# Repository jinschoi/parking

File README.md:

Ultrasonic Parking Aid
=======

Parking aid using the SR-04 ultrasonic distance sensor to indicate distance via LEDs. Low-power, AA battery powered, 3D printable enclosure suggestion available.

Green LED indicates go until yellow LED gets triggered at a set distance. Yellow LED blinks with a rate proportional to distance until red LED distance is crossed. LED blinking rate is implemented using TIMER1.

Low power mode is entered when no forward motion events have been detected for 5 seconds. Motion away from sensor is ignored so as not to trigger when backing away.

Libraries Required
-----

_Sleepy_ library from [jeelib](http://jeelabs.net/projects/jeelib/wiki) is used to reduce power usage when idling.

[NewPing](https://code.google.com/p/arduino-new-ping/) library is required for interfacing with the ultrasonic sensor.

Full description at [hackaday.io](http://hackaday.io/project/1218-Ultrasonic-Parking-Aid-without-Arduino).

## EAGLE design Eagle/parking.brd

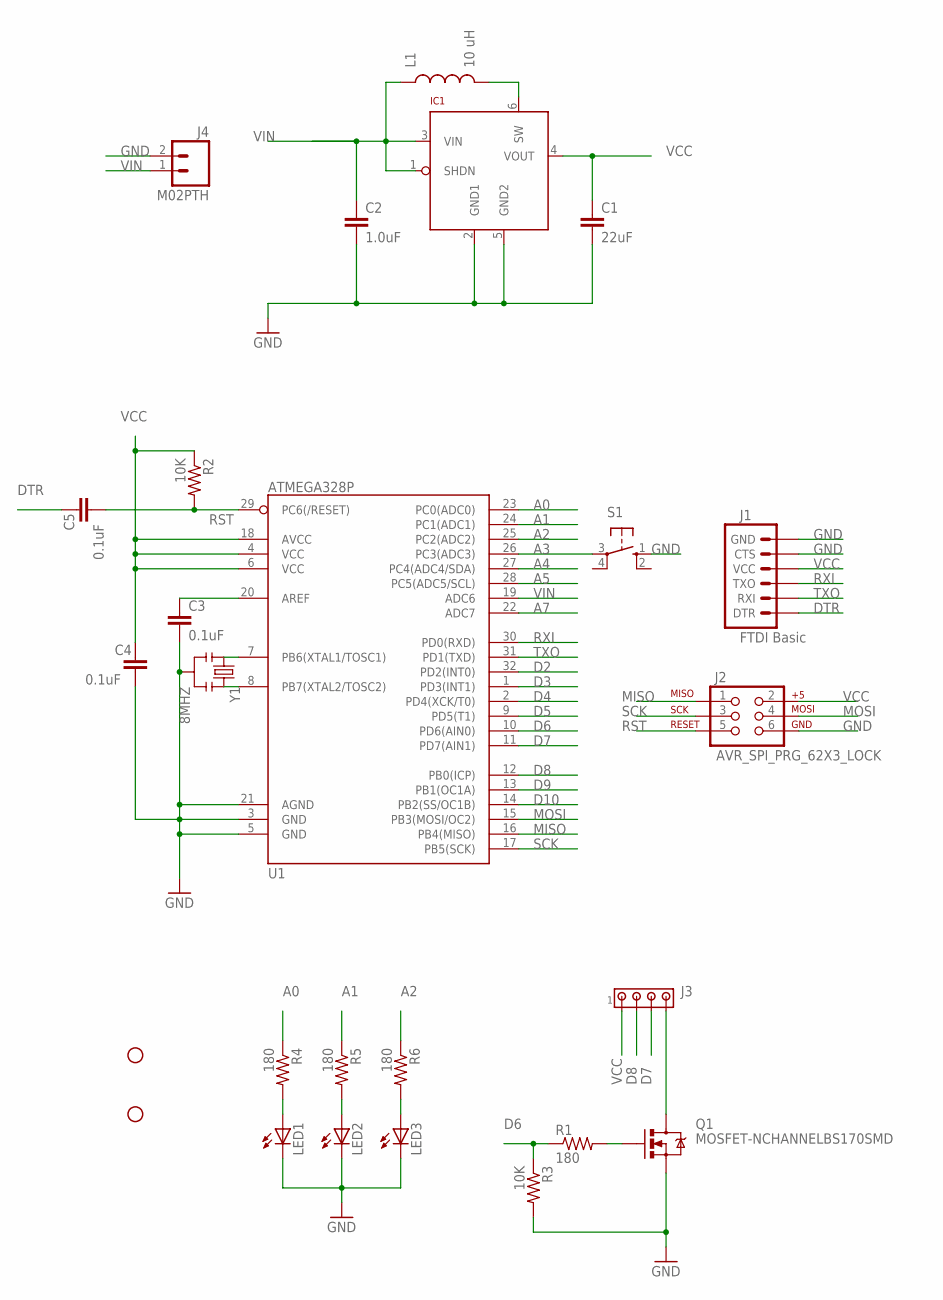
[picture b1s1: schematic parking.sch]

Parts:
C1: 22uF; 0805
C2: 1.0uF; 0805
C3, C4, C5: 0.1uF; 0805
IC1: LTC3525; SC70
J1: FTDI Basic; 1X06
J2: AVR_SPI_PRG_62X3_LOCK; 2X3_LOCK
J3: MTA04-100; 10X04MTA
J4: M02PTH; 1X02
L1: 10 uH; 1210
LED1, LED2, LED3: LED5MM
Q1: MOSFET-NCHANNELBS170SMD; SOT23
R1, R4, R5, R6: 180; 0805
R2, R3: 10K; 0805
S1: 10-XX; B3F-10XX
STANDOFF1, STANDOFF2: STAND-OFF
U1: ATMEGA328P; TQFP32-08
Y1: 8MHZ; RESONATOR-SMD

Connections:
A0: R4.1, U1.23 (PC0(ADC0))
A1: R5.1, U1.24 (PC1(ADC1))
A2: R6.1, U1.25 (PC2(ADC2))
A3: S1.3, U1.26 (PC3(ADC3))
A4: U1.27 (PC4(ADC4/SDA))
A5: U1.28 (PC5(ADC5/SCL))
A7: U1.22 (ADC7)
D2: U1.32 (PD2(INT0))
D3: U1.1 (PD3(INT1))
D4: U1.2 (PD4(XCK/T0))
D5: U1.9 (PD5(T1))
D6: R1.1, R3.1, U1.10 (PD6(AIN0))
D7: J3.3, U1.11 (PD7(AIN1))
D8: J3.2, U1.12 (PB0(ICP))
D9: U1.13 (PB1(OC1A))
D10: U1.14 (PB2(SS/OC1B))
DTR: C5.1, J1.1 (DTR)
GND: C1.2, C2.2, C3.2, C4.2, IC1.2 (GND1), IC1.5 (GND2), J1.5 (CTS), J1.6 (GND), J2.6, J4.2, LED1.K (C), LED2.K (C), LED3.K (C), Q1.2 (S), R3.2, S1.1 (S), U1.3 (GND), U1.5 (GND), U1.21 (AGND), Y1.2
MISO: J2.1, U1.16 (PB4(MISO))
MOSI: J2.4, U1.15 (PB3(MOSI/OC2))
unnamed: U1.8 (PB7(XTAL2/TOSC2)), Y1.3
unnamed: U1.7 (PB6(XTAL1/TOSC1)), Y1.1
unnamed: IC1.6 (SW), L1.2
unnamed: C3.1, U1.20 (AREF)
unnamed: LED1.A, R4.2
unnamed: LED2.A, R5.2
unnamed: LED3.A, R6.2
unnamed: J3.4, Q1.3 (D)
unnamed: Q1.1 (G), R1.2
RST: C5.2, J2.5, R2.2, U1.29 (PC6(/RESET))
RXI: J1.3 (TXO), U1.30 (PD0(RXD))
SCK: J2.3, U1.17 (PB5(SCK))
TXO: J1.2 (RXI), U1.31 (PD1(TXD))
VCC: C1.1, C4.1, IC1.4 (VOUT), J1.4 (VCC), J2.2, J3.1, R2.1, U1.4 (VCC), U1.6 (VCC), U1.18 (AVCC)
VIN: C2.1, IC1.1 (SHDN), IC1.3 (VIN), J4.1, L1.1, U1.19 (ADC6)

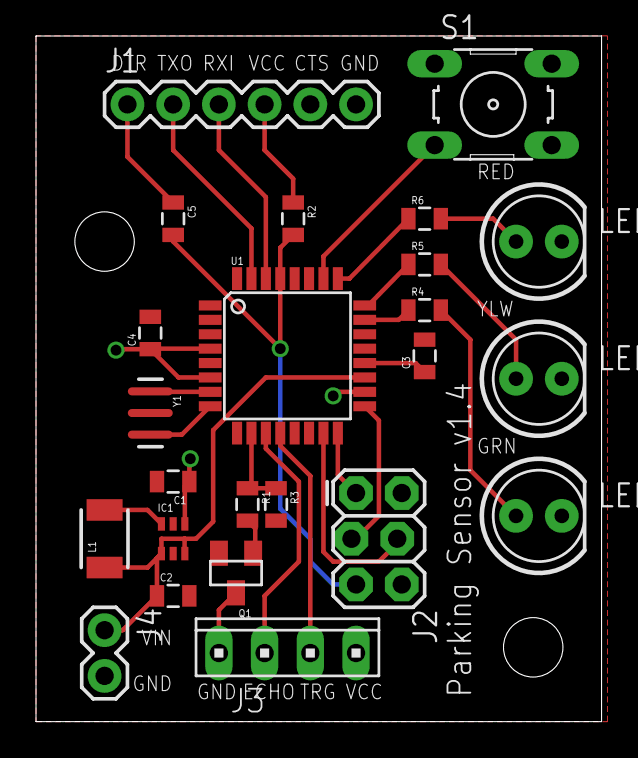
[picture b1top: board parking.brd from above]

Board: 2 copper layers, 31.4 x 38.1 mm, 26 parts (0 on the bottom side), 26 nets.

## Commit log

2014-05-23 Added project files.
2014-05-23 Fixed links in README.
2014-05-23 Moved Arduino sketch to toplevel.
2014-05-23 Improved idle detection logic.
2014-05-25 Distinguish between idle states of "parked car" and "no car".
2014-05-25 Diagnostic blinks on pings in idle states.
2014-05-25 Revised enclosure.
2014-05-26 Fixed misrouted trace for bypass capacitor.
2014-06-10 Changed resonator footprint, modified ping sensor VCC to be switched from a pin to save power.
2014-07-01 Added low side MOSFET switch to power down the sensor.
2014-07-19 Updated sketch for revision 1.3 of the board, with MOSFET sensor switch and VIN trace.
2014-07-19 Fixed stupid battery voltage reading bug.
2014-07-20 Updated enclosure files for 1.3
2014-07-25 Added alternative side-by-side enclosure design files.
2014-10-13 Explicitly set last_distance when transitioning to PARKING from WAITING.
2015-01-02 Revision 1.4 of the board. Includes a pushbutton to calibrate red light distance.

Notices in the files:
parts and their libraries:
SparkFun-DigitalIC: Licensing: Creative Commons ShareAlike 4.0 International - https://creativecommons.org/licenses/by-sa/4.0
